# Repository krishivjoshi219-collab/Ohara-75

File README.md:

# Ohara-75 !!!!!!!!!!!!!!!!!!!!!!!!!!!

> A e-ink-reader !!!!!!!!!!!!!!! with one piece features !!!!!!!!!! powered by esp32 and a e-paper screen for reading manga or novels with 0 eye strain

**hi this is my first readme for my 3rd pcb project !!!!!!!! pls dont judge my spelling i am 13 and i type too fast :sob:**
**also this is the same voice as my JOURNAL.md because that is just how i write ok !!!!!!!**

---

## WAIT WHAT IS THIS?????

Ohara-75 is a handheld e-ink reader i made for reading **MANGA** and novels with **0 eye strain** !!!!!!!!!

it has a 7.5 inch e-paper screen, an ESP32-S3, a microSD card for all my offline books, a LiPo battery, USB-C charging, two Kailh Choc page buttons, and a 3D printed case. it is 98x98mm because JLCPCB is cheap only until the 100x100 limit !!!!!!! (i wanted a straw hat shaped edge cut at first but then i realized a e-reader needs a rectangle :C)

i am planning to use this for my entire school years so it is not just SOME project for me !!!!!!!!!!!

---

## FEATURES !!!!!!!!!

- 7.5 inch e-paper, 800x480, 1-bit, 0 eye strain when reading at 2am
- ESP32-S3-WROOM-1 running MicroPython
- microSD card slot (i have a 32GB card for offline manga/novels)
- USB-C for charging and programming
- TP4056 LiPo charger + AP2112K 3.3V regulator
- LiPo battery connector (JST PH)
- 2x Kailh Choc page buttons because turning pages with a 5-way is slow
- 5-way navigation header (up/down/left/right/press)
- power switch, reset button, boot button
- silkscreen labels for every port: USB-C, microSD, EPD, BATT, NAV, plus every nav pin (UP/DOWN/LEFT/RIGHT/PRESS/GND), battery pins (VBAT/GND), and NEXT/PREV/PWR/BOOT/RESET
- 3D printed base tray + lid (STLs are in `3d/`)
- U-shaped USB-C cable hole in the base tray !!!!!!!!!

---

## THE USB-C CABLE HOLE !!!!!!!!!

the USB-C port is on the bottom edge of the PCB, so i added a little U-shaped pass-through in the base tray. it is 14mm wide and 8mm tall, centered at **x = 140.75mm** (same as the USB-C connector), and it goes through the 2.2mm front wall. now a USB-C cable can loop up into the port without drilling a ugly hole myself !!!!!!!!!

the file is `3d/Ohara-75-Base-Tray.stl`. the lid is `3d/Ohara-75-Lid.stl`.

---

## SILKSCREEN PIN LABELS !!!!!!!!!

i labeled the pins like i did on my Starbie and Tone Dial boards. headers get one label per pin so you dont have to keep the schematic open while soldering !!!!!!!!

| port | labels |
| :--- | :--- |
| **J5 NAV 6-pin** | 1 UP · 2 DOWN · 3 LEFT · 4 RIGHT · 5 PRESS · 6 GND |
| **J4 BATT 2-pin** | 1 VBAT · 2 GND |
| **J1 EPD FPC** | `EPD` + pin-1 marker (0.5mm pitch is too tiny for all 24 labels) |
| **J2 microSD** | `microSD` |
| **J3 USB-C** | `USB-C` |

the page buttons and power switch are also labeled `NEXT`, `PREV`, and `PWR`, and the tiny buttons are `BOOT` and `RESET`. all of this is on the **front silkscreen**.

---

## THE BIG Q1 OOPS !!!!!!!!! (READ THIS BEFORE YOU BUILD)

ok so this is the part where i have to be honest. the MOSFET Q1 on the PCB is wired wrong in the current netlist.

**current / wrong wiring:**

- Q1 pin 1 (G) -> switch node
- Q1 pin 2 (S) -> `/EPD_GDR`
- Q1 pin 3 (D) -> `/EPD_RESE`

**correct wiring:**

- Q1 pin 1 (G) -> `/EPD_GDR`
- Q1 pin 2 (S) -> `/EPD_RESE`
- Q1 pin 3 (D) -> switch node (the L1/D1 side)

if you build the board as-is the e-paper boost supply will not work and the screen will stay white. you need to rework Q1 or add jumper wires. i found this with my dad while checking the schematic and i am fixing it in the next revision !!!!!!!! **DO NOT FORGET THIS PART !!!!!!!!!**

---

## FILES IN THIS REPO !!!!!!!!!

```text
Ohara-75.kicad_pcb        the PCB (with port labels on the silkscreen)
Ohara-75.kicad_sch        the schematic
Ohara-75.kicad_pro        KiCad project
Ohara-75.step             PCB 3D model
Ohara-75.pretty/          my custom footprints
fp-lib-table              footprint library table
JOURNAL.md                my Half Life devlog (the origin of this readme voice)
BOM.csv                   bill of materials ($67.93 total, fits Hack Club grant budget)
firmware/frimware.py      the simple ~100 line beginner firmware
firmware/archive/         the full production firmware
3d/Ohara-75-Base-Tray.stl base tray with the USB-C U-hole
3d/Ohara-75-Lid.stl       front lid / bezel
images/                   renders used in this readme
```

---

## HOW TO BUILD IT !!!!!!!!!

1. **Order the PCB.** it is 98x98mm so it fits the cheap JLCPCB size. use 1.6mm thickness and HASL is fine.
2. **Solder everything.** ESP32-S3, USB-C, microSD, EPD FPC connector, TP4056, AP2112K, passives, buttons, battery connector. the FPC connector is 0.5mm pitch so please use flux and a microscope if you have one.
3. **FIX Q1.** read the big warning above. G -> `/EPD_GDR`, S -> `/EPD_RESE`, D -> switch node.
4. **Print the case.** print `3d/Ohara-75-Base-Tray.stl` and `3d/Ohara-75-Lid.stl`. the base already has the USB-C cable hole.
5. **Flash MicroPython** for the ESP32-S3.
6. **Copy the firmware.** the simple one is `firmware/frimware.py`. copy it to the board and rename it to `main.py` (or import it from your own `main.py`). the full one is in `firmware/archive/firmware_production.py` if you want menus, bookmarks, settings, sleep, etc.
7. **Copy books to the SD card.** for the simple firmware make a FAT32 card with `/sd/book.txt`. for the full firmware use `/sd/books/` and put `.txt` or `.md` files there.
8. **Plug in USB-C and pray.** if the screen is white, check Q1 first. i am serious !!!!!!!!

---

## HOW TO USE IT !!!!!!!!!

### Simple firmware (`firmware/frimware.py`)

- **NEXT** / **PREV** page buttons turn pages
- it reads `/sd/book.txt`
- it uses fixed-width wrapping (it does not do fancy word wrap, sorry)
- no menus, no settings, no bookmarks, no sleep. just reading !!!!!!!!

### Full firmware (`firmware/archive/firmware_production.py`)

- **UP / DOWN** move in menus
- **PRESS** select
- **LEFT** back
- **NEXT / PREV** or **LEFT / RIGHT** turn pages in the reader
- **PRESS** in the reader opens the book menu
- bookmarks, jump to page, settings, theme, line spacing, fast/full refresh, auto sleep, SD progress saving !!!!!!!!

---

## WHAT WENT WRONG / TODO !!!!!!!!!

- [x] design the PCB
- [x] route the PCB
- [x] make the case
- [x] add the USB-C cable hole
- [x] add port labels to the silkscreen
- [x] write the simple firmware
- [x] write the full firmware
- [ ] **FIX Q1 AND ORDER REV 2** (this is the big one)
- [ ] test the e-paper on real hardware
- [ ] add manga/CBZ support (right now it is text only, sorry)
- [ ] add a battery voltage divider so the battery percentage actually works
- [ ] make the case look nicer (maybe straw hat vents next time?)
- [ ] read way too much manga and call it testing

---

## WHY I MADE THIS

i wanted a e-reader that i can use for school and for manga without staring at a bright LCD all day. i researched the ESP32-S3 and the 7.5 inch e-paper, picked a 32GB microSD so i can read offline, and designed the whole thing in KiCad. this is my 3rd PCB and it was really hard to manage the schematic, placement, routing, DRC errors, and the case all at once !!!!!!!!

the routing was a **PDB DEADLOCK** at one point :C and i had like 50 DRC errors at the end. most of them were thermal relief and minimum drill hole stuff. i fixed them and rounded my hours to a clean number because messy numbers are annoying.

also i wanted a straw hat shaped edge cut like my week 1 starbie and week 3 tone dial, but a e-reader needs a rectangle so i used a normal rounded rectangle. maybe rev 2 gets a straw hat logo on the silkscreen instead !!!!!!!!

---

## THANKS !!!!!!!!!

- **Hack Club / Half Life** for making me actually finish this
- all the **HC reviewers** who read my devlog (sorry for the spelling)
- my dad for helping me find the Q1 problem
- **Waveshare** for the MIT licensed 7.5 inch e-paper init code
- **KiCad**, **JLCPCB**, and everyone who answered my questions
- and you for reading this README !!!!!!!!!!!!!!!!!!

---

## LICENSE

the e-paper init sequences are adapted from Waveshare's MIT licensed driver, so those bits stay MIT. everything else is my project. if you build one please credit me and send me a picture !!!!!!!! i am not a lawyer lol.

**Thx for reading !!!!!!!! :D**

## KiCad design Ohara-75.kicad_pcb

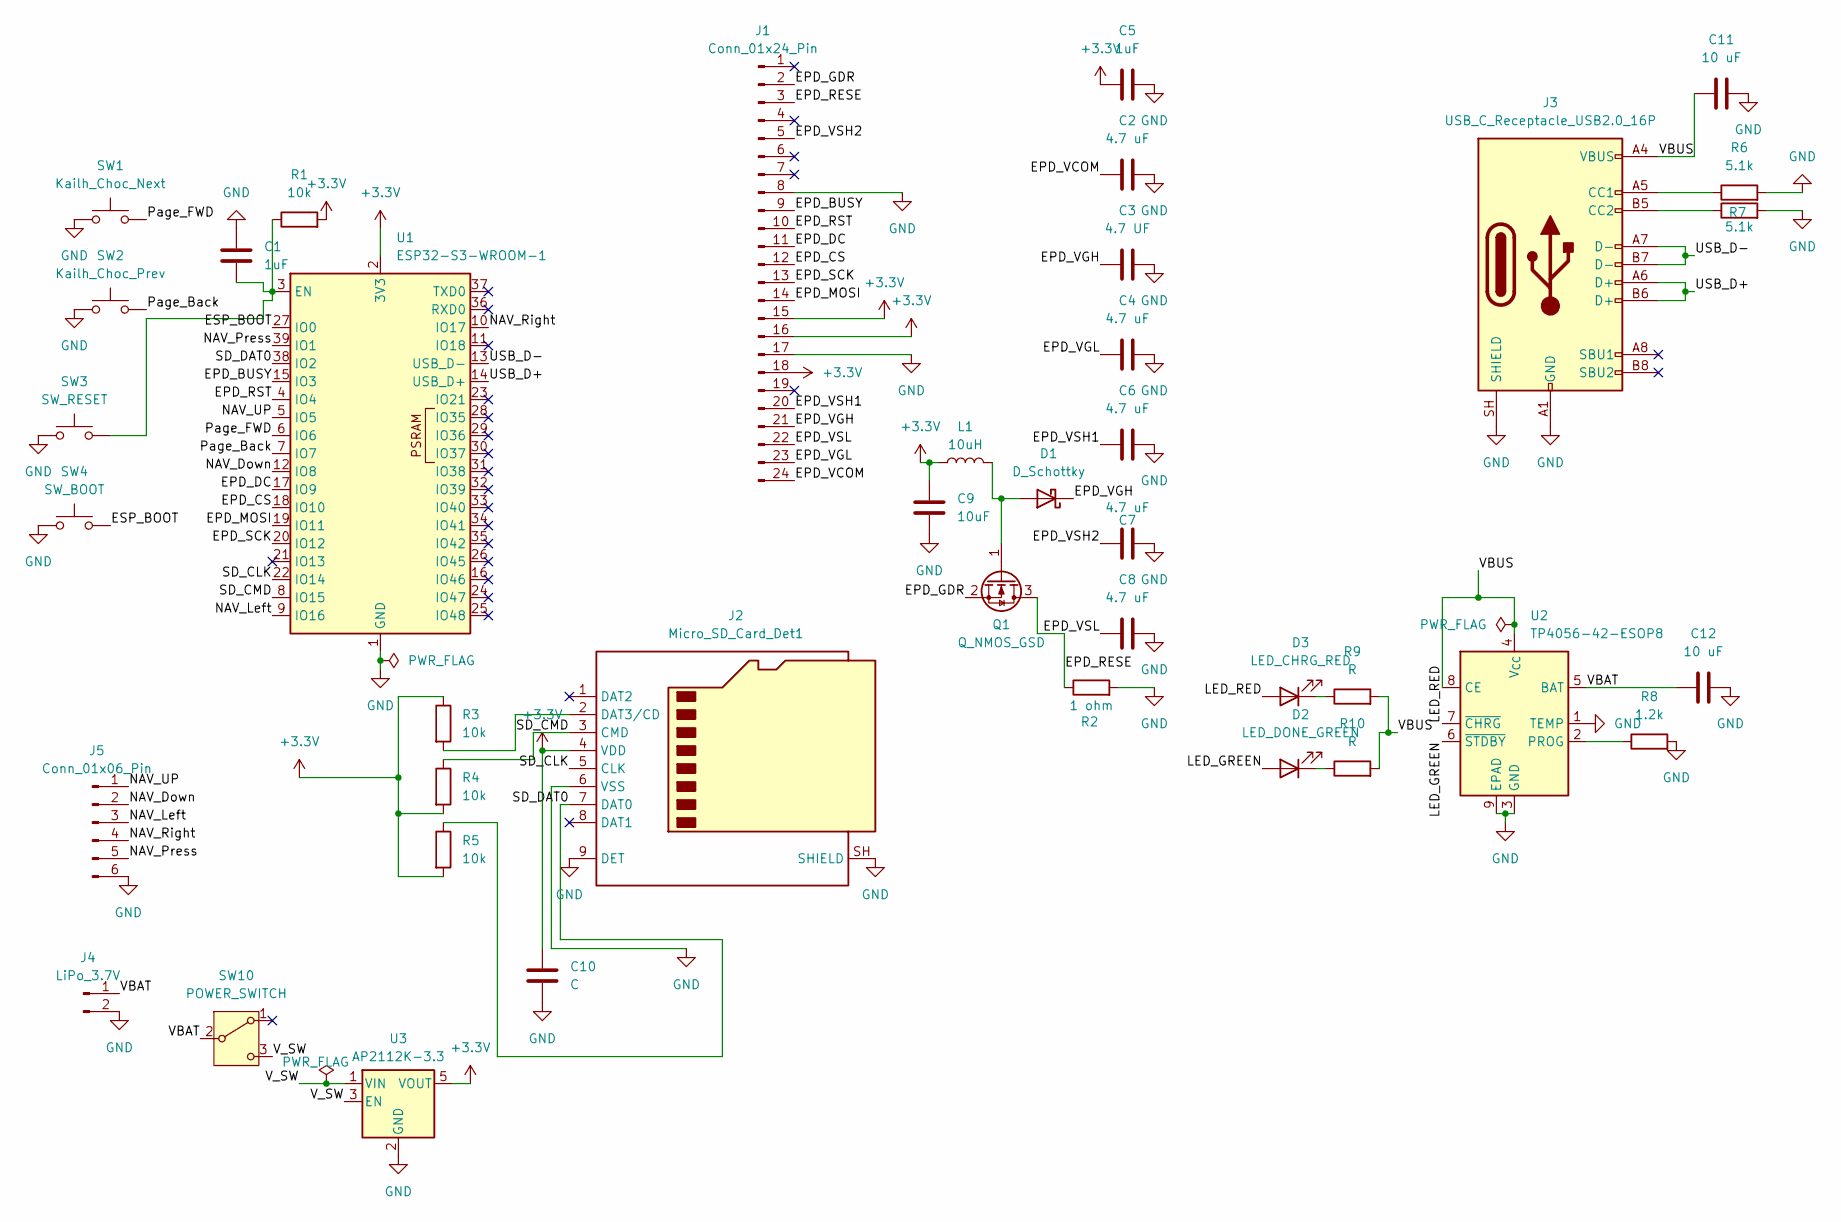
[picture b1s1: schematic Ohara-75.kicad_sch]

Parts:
C1, C5: 1uF; C_0805_2012Metric
C2, C4, C6, C7, C8: 4.7 uF; C_0805_2012Metric
C3: 4.7 UF; C_0805_2012Metric
C9: 10uF; C_0805_2012Metric
C10: C; C_0805_2012Metric
C11, C12: 10 uF; C_0805_2012Metric
D1: D_Schottky; D_SOD-123
D2: LED_DONE_GREEN; LED_0805_2012Metric
D3: LED_CHRG_RED; LED_0805_2012Metric
J1: Conn_01x24_Pin; Hirose_FH12-24S-0.5SH_1x24-1MP_P0.50mm_Horizontal
J2: Micro_SD_Card_Det1; microSD_XKB_XKTF-015-N
J3: USB_C_Receptacle_USB2.0_16P; USB_C_Receptacle_HRO_TYPE-C-31-M-12
J4: LiPo_3.7V; JST_PH_B2B-PH-K_1x02_P2.00mm_Vertical
J5: Conn_01x06_Pin; PinHeader_1x06_P2.54mm_Vertical
L1: 10uH; L_1210_3225Metric
Q1: Q_NMOS_GSD; SOT-23
R1, R3, R4, R5: 10k; R_0805_2012Metric
R2: 1 ohm; R_0805_2012Metric
R6, R7: 5.1k; R_0805_2012Metric
R8: 1.2k; R_0805_2012Metric
R9, R10: R; R_0805_2012Metric
SW1: Kailh_Choc_Next; SW_Kailh_Choc_v1
SW2: Kailh_Choc_Prev; SW_Kailh_Choc_v1
SW3: SW_RESET; SW_SPST_EVQP7A
SW4: SW_BOOT; SW_SPST_EVQP7A
SW10: POWER_SWITCH; SW_SPDT_Shouhan_MSK12C02
U1: ESP32-S3-WROOM-1
U2: TP4056-42-ESOP8; SOIC-8-1EP_3.9x4.9mm_P1.27mm_EP2.41x3.3mm_ThermalVias
U3: AP2112K-3.3; SOT-23-5

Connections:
+3.3V: C5.1, C9.1, C10.1, J1.15, J1.16, J1.18, J2.4 (VDD), L1.1, R1.2, R3.1, R4.2, R5.2, U1.2 (3V3), U3.5 (VOUT)
/EPD_BUSY: J1.9, U1.15 (IO3)
/EPD_CS: J1.12, U1.18 (IO10)
/EPD_DC: J1.11, U1.17 (IO9)
/EPD_GDR: J1.2, Q1.2 (S)
/EPD_MOSI: J1.14, U1.19 (IO11)
/EPD_RESE: J1.3, Q1.3 (D), R2.1
/EPD_RST: J1.10, U1.4 (IO4)
/EPD_SCK: J1.13, U1.20 (IO12)
/EPD_VCOM: C2.1, J1.24
/EPD_VGH: C3.1, D1.1 (K), J1.21
/EPD_VGL: C4.1, J1.23
/EPD_VSH1: C6.1, J1.20
/EPD_VSH2: C7.1, J1.5
/EPD_VSL: C8.1, J1.22
/ESP_BOOT: SW4.2, U1.27 (IO0)
/LED_GREEN: D2.2 (A), U2.6 (~STDBY)
/LED_RED: D3.2 (A), U2.7 (~CHRG)
/NAV_Down: J5.2, U1.12 (IO8)
/NAV_Left: J5.3, U1.9 (IO16)
/NAV_Press: J5.5, U1.39 (IO1)
/NAV_Right: J5.4, U1.10 (IO17)
/NAV_UP: J5.1, U1.5 (IO5)
/Page_Back: SW2.2, U1.7 (IO7)
/Page_FWD: SW1.2, U1.6 (IO6)
/SD_CLK: J2.5 (CLK), U1.22 (IO14)
/SD_CMD: J2.3 (CMD), R4.1, U1.8 (IO15)
/SD_DAT0: J2.7 (DAT0), R5.1, U1.38 (IO2)
/USB_D+: J3.A6 (D+), J3.B6 (D+), U1.14 (USB_D+)
/USB_D-: J3.A7 (D-), J3.B7 (D-), U1.13 (USB_D-)
/VBAT: C12.1, J4.1, SW10.2 (B), U2.5 (BAT)
/VBUS: C11.1, J3.A4 (VBUS), J3.A9 (VBUS), J3.B4 (VBUS), J3.B9 (VBUS), R9.2, R10.2, U2.4 (V_{CC}), U2.8 (CE)
/V_SW: SW10.3 (C), U3.1 (VIN), U3.3 (EN)
GND: C1.1, C2.2, C3.2, C4.2, C5.2, C6.2, C7.2, C8.2, C9.2, C10.2, C11.2, C12.2, J1.8, J1.17, J2.6 (VSS), J2.9 (DET), J2.SH (SHIELD), J3.A1 (GND), J3.A12 (GND), J3.B1 (GND), J3.B12 (GND), J3.SH (SHIELD), J4.2, J5.6, R2.2, R6.2, R7.2, R8.2, SW1.1, SW2.1, SW3.1, SW4.1, U1.1 (GND), U1.40 (GND), U1.41 (GND), U2.1 (TEMP), U2.3 (GND), U2.9 (EPAD), U3.2 (GND)
unnamed: D1.2 (A), L1.2, Q1.1 (G)
unnamed: D2.1 (K), R10.1
unnamed: D3.1 (K), R9.1
unnamed: J2.2 (DAT3/CD), R3.2
unnamed: J3.A5 (CC1), R6.1
unnamed: J3.B5 (CC2), R7.1
unnamed: C1.2, R1.1, SW3.2, U1.3 (EN)
unnamed: R8.1, U2.2 (PROG)

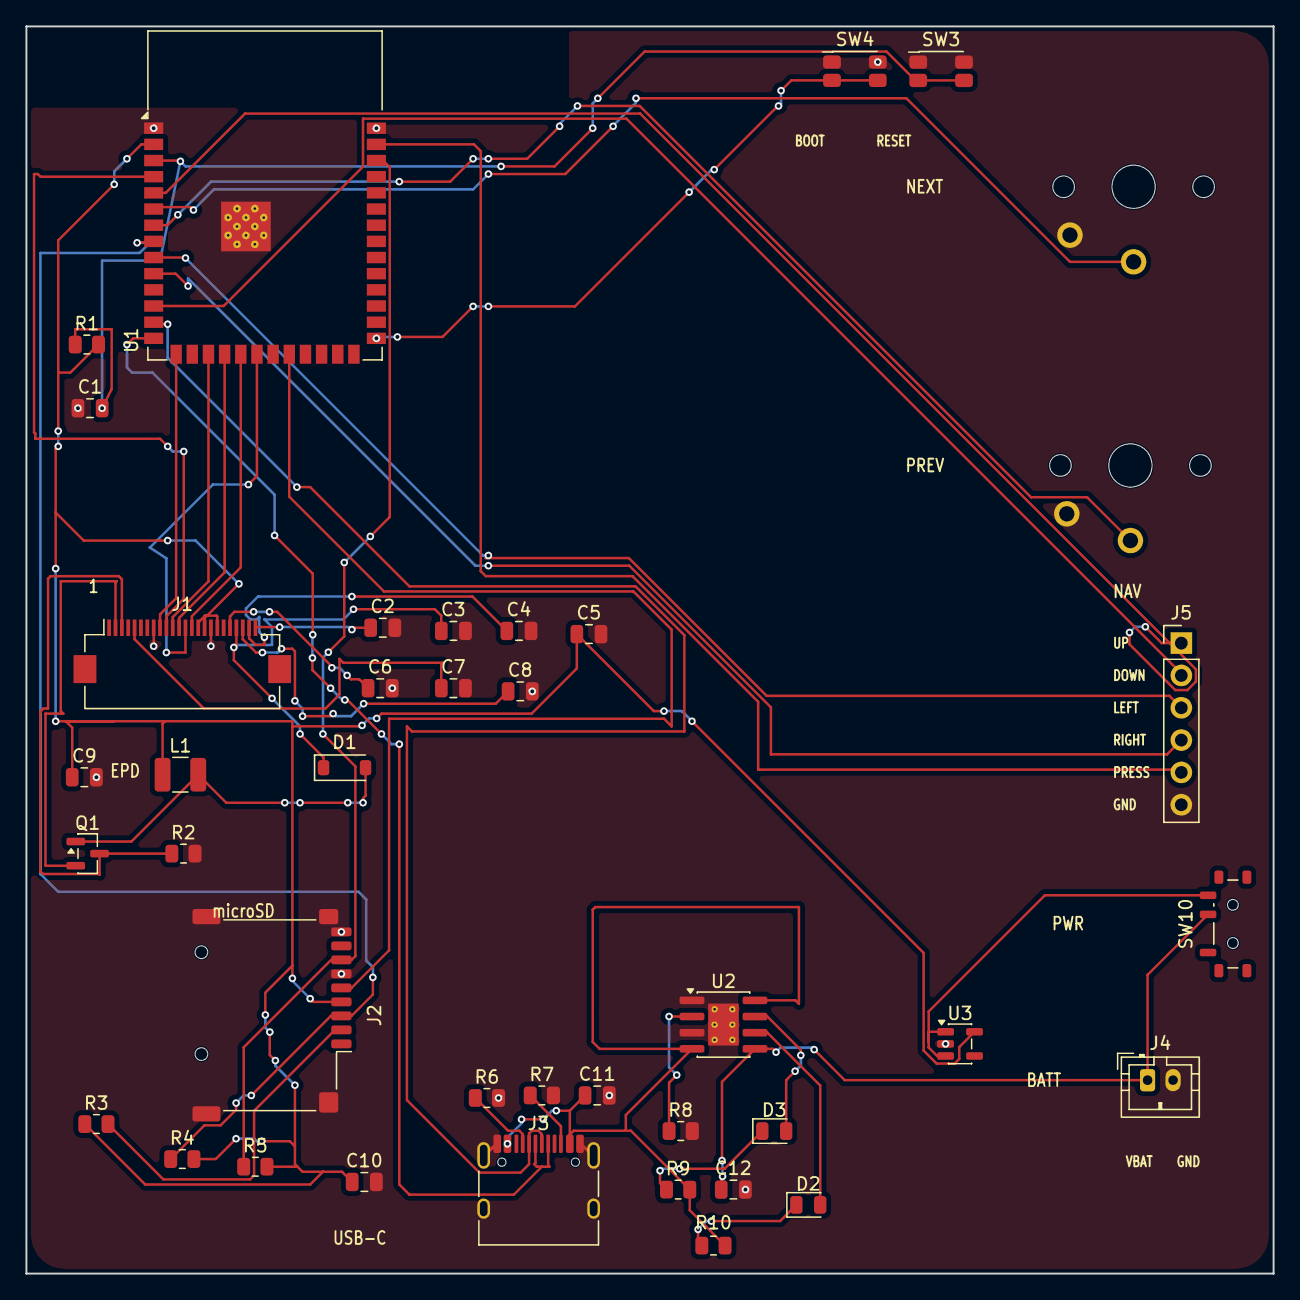
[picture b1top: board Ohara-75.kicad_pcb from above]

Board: 2 copper layers, 98.0 x 98.0 mm, 40 parts (0 on the bottom side), 42 nets.

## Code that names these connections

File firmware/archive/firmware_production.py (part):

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HEIGHT = 480
BUF = WIDTH * HEIGHT // 8

EPD_SCK = 12
EPD_MOSI = 11
EPD_CS = 10
EPD_DC = 9
EPD_RST = 4
EPD_BUSY = 3

BTN_NEXT = 6
BTN_PREV = 7
NAV_UP = 5
NAV_DOWN = 8
NAV_LEFT = 16
NAV_RIGHT = 17
NAV_PRESS = 1

BOOKS_DIR = "/sd/books"
STATE_DIR = "/sd/.ohara"
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class Buttons:
    def __init__(self):
        self.pins = {
            "up": machine.Pin(NAV_UP, machine.Pin.IN, machine.Pin.PULL_UP),
            "down": machine.Pin(NAV_DOWN, machine.Pin.IN, machine.Pin.PULL_UP),
            "left": machine.Pin(NAV_LEFT, machine.Pin.IN, machine.Pin.PULL_UP),
            "right": machine.Pin(NAV_RIGHT, machine.Pin.IN, machine.Pin.PULL_UP),
            "press": machine.Pin(NAV_PRESS, machine.Pin.IN, machine.Pin.PULL_UP),
            "next": machine.Pin(BTN_NEXT, machine.Pin.IN, machine.Pin.PULL_UP),
            "prev": machine.Pin(BTN_PREV, machine.Pin.IN, machine.Pin.PULL_UP),
        }
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    def __init__(self):
        spi = machine.SPI(
            1, baudrate=4000000, polarity=0, phase=0,
            sck=machine.Pin(EPD_SCK), mosi=machine.Pin(EPD_MOSI)
        )
        self.epd = EPD(
            spi,
            machine.Pin(EPD_CS), machine.Pin(EPD_DC),
            machine.Pin(EPD_RST), machine.Pin(EPD_BUSY)
        )
        self.buttons = Buttons()
        self.storage = Storage()
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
